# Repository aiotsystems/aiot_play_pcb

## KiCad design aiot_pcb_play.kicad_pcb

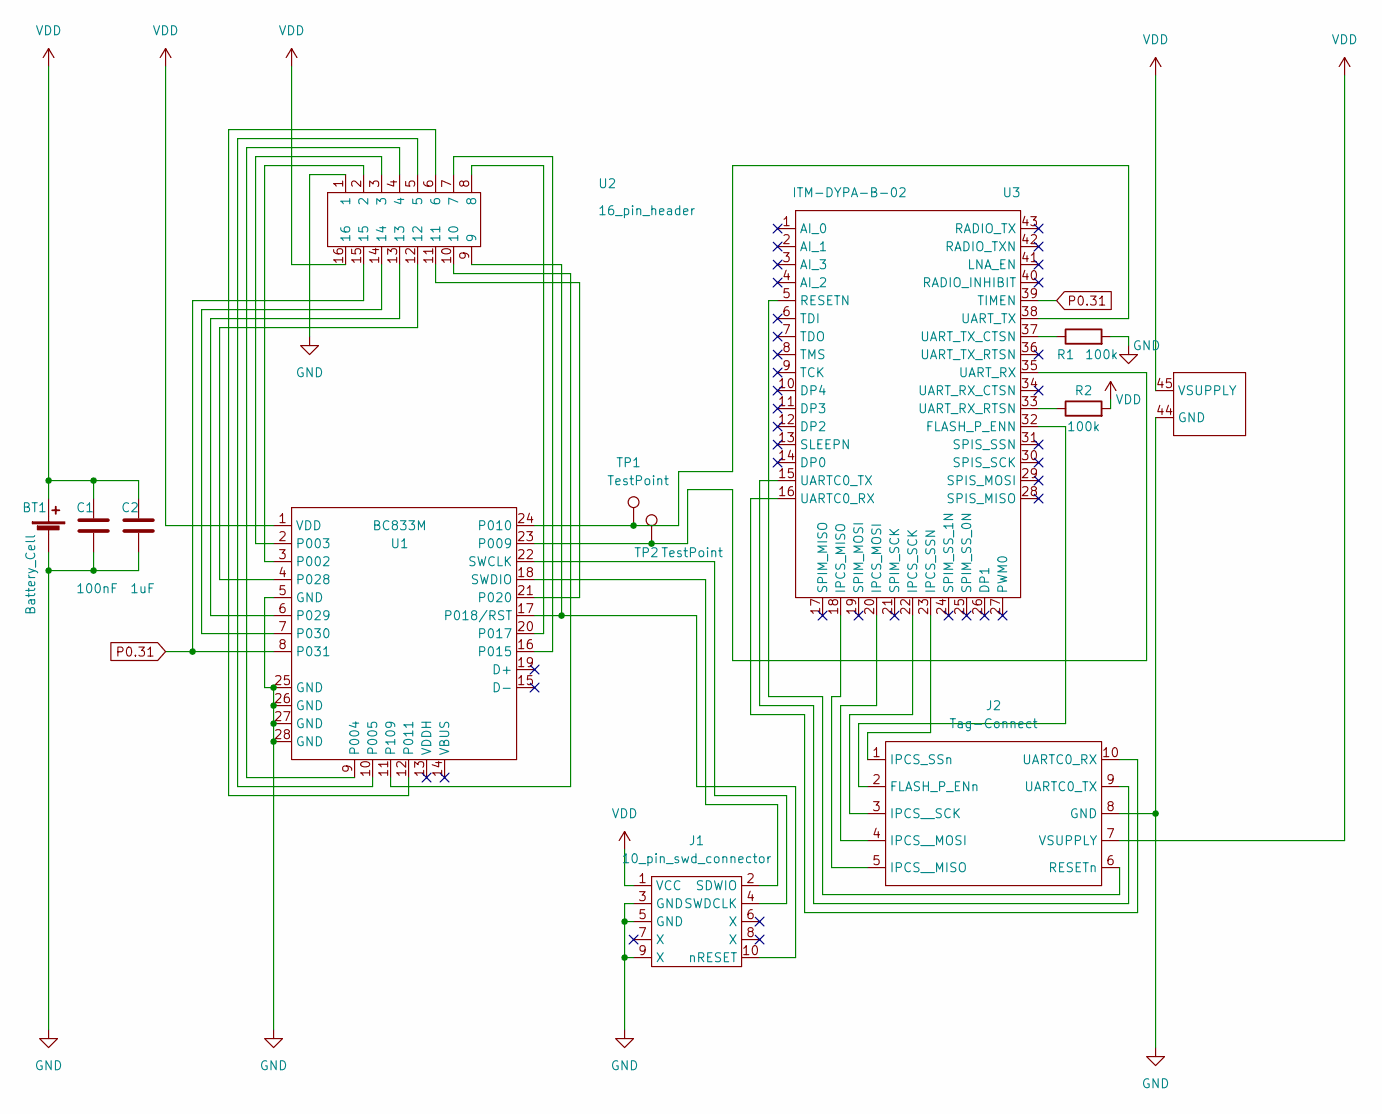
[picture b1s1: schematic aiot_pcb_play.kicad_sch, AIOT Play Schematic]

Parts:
BT1: Battery_Cell; BatteryHolder_MPD_BC2AAPC_2xAA
C1: 100nF; C_0603_1608Metric
C2: 1uF; C_0603_1608Metric
J1: 10_pin_swd_connector; Samtec_Connector_FTSH-105-01-F-DV-K
J2: Tag-Connect; tag-connect_10_pins_no_hooks
R1, R2: 100k; R_0603_1608Metric
TP1, TP2: TestPoint; test_pad
U1: BC833M
U2: 16_pin_header; 16_pin_connector
U3: ITM-DYPA-B-02; dusty_pcb_ant

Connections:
GND: BT1.2 (-), C1.2, C2.2, J1.3 (GND), J1.5 (GND), J1.9 (X), J2.8 (GND), R1.2, U1.5 (GND), U1.25 (GND), U1.26 (GND), U1.27 (GND), U1.28 (GND), U2.1, U3.44 (GND)
unnamed: J1.2 (SDWIO), U1.18 (SWDIO)
unnamed: J1.4 (SWDCLK), U1.22 (SWCLK)
unnamed: J1.10 (nRESET), U1.17 (P018/RST), U2.9
unnamed: J2.2 (FLASH_P_ENn), U3.32 (FLASH_P_ENN)
unnamed: J2.1 (IPCS_SSn), U3.23 (IPCS_SSN)
unnamed: J2.5 (IPCS__MISO), U3.18 (IPCS_MISO)
unnamed: J2.4 (IPCS__MOSI), U3.20 (IPCS_MOSI)
unnamed: J2.3 (IPCS__SCK), U3.22 (IPCS_SCK)
unnamed: J2.6 (RESETn), U3.5 (RESETN)
unnamed: J2.10 (UARTC0_RX), U3.16 (UARTC0_RX)
unnamed: J2.9 (UARTC0_TX), U3.15 (UARTC0_TX)
unnamed: U1.3 (P002), U2.2
unnamed: U1.2 (P003), U2.3
unnamed: U1.9 (P004), U2.4
unnamed: U1.10 (P005), U2.5
unnamed: TP2.1, U1.23 (P009), U3.35 (UART_RX)
unnamed: TP1.1, U1.24 (P010), U3.38 (UART_TX)
unnamed: U1.12 (P011), U2.6
unnamed: U1.16 (P015), U2.7
unnamed: U1.20 (P017), U2.8
unnamed: U1.21 (P020), U2.11
unnamed: U1.4 (P028), U2.12
unnamed: U1.6 (P029), U2.13
unnamed: U1.7 (P030), U2.14
unnamed: U1.11 (P109), U2.10
unnamed: R2.1, U3.33 (UART_RX_RTSN)
unnamed: R1.1, U3.37 (UART_TX_CTSN)
P0.31: U1.8 (P031), U2.15, U3.39 (TIMEN)
VDD: BT1.1 (+), C1.1, C2.1, J1.1 (VCC), J2.7 (VSUPPLY), R2.2, U1.1 (VDD), U2.16, U3.45 (VSUPPLY)

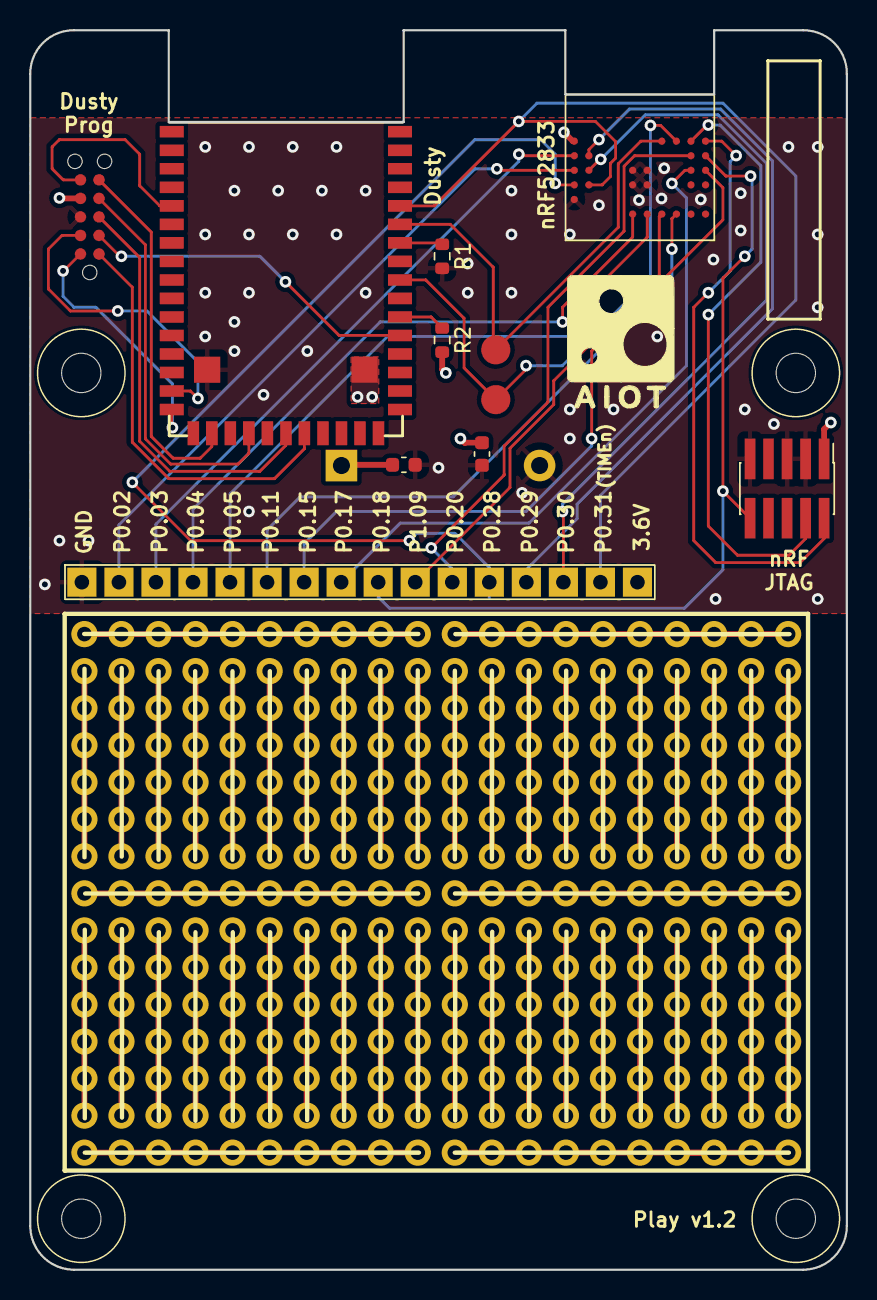
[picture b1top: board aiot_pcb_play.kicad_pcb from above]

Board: 4 copper layers, 56.0 x 85.0 mm, 12 parts (1 on the bottom side), 30 nets.

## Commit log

2022-05-17 v1.0
2022-10-17 #1 Fix added missing flow control connections to the Schematics
2022-10-17 #1 Explicitly mark as disconnected, all disconnected pins in the schematics
2022-10-17 Fix: Add suitable .gitignore to the project
2022-10-17 #1 Fix: Dependencies to missing footprint libraries
    The library with the footprints for the Dusty module and the BCM833 were not in the repository
2022-10-17 #1 Made changes to the PCB
2022-10-17 #1 Fix: Mounting holes not detected by PCB manufacturer
    Eurocircuits was not registering the Mounting holes on the PCB, so I changed the footprint
2022-10-18 Doc: Updated version number in schematic title
    and in the pcb too.
    v1.0 to v1.1
2022-10-18 Doc: Add pdf version of the schematic and pcb layout
2023-11-30 Finished the design of the AIOT Play v1.2 addressing #5 and #6
2023-11-30 adding the schematics file
2023-11-30 #4 silkscreen changed p0.19->p1.09
2023-11-30 adding the v1.2 GERBER to the output folder
2023-11-30 #4 changed p0.19->p1.09 on the simbol in the schematics pdf
